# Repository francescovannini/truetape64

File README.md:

# TrueTape64

A cheap, easy to build adapter to interface a [Commodore 1530 (C2N) Datasette ](https://en.wikipedia.org/wiki/Commodore_Datasette) to your PC to dump and preserve your aging Commodore 64 software collection, as accurately as possible.

## What?!

Back in the '80s, many home computers used audio cassette tapes as a medium to to store data. Floppy disks already existed but they often required complex, dedicated hardware; tapes and tape decks on the other hand were cheap, common medium used for music and required simpler or in some cases (like Apple-II) no extra hardware or peripheral. Data was stored encoded as audio and it sounded very similar to the well-known squeaky modem / fax sounds. This storage method had obviously several downsides: long loading/saving times, wasn't "random access" so it required the user to manually advance the tape to the right position to access the desired file; and reliability depended a lot on the quality of the tape. But all these were more than acceptable compromises to keep the prices of these systems down and give everyone a cheap, good-enough way to access or build large software libraries.

As many other future developers born in the '80s, I've started writing BASIC code on a [Commodore 64](https://en.wikipedia.org/wiki/Commodore_64) when I was just a kid. Being still today a huge fan of this platform and having a large collection of tapes, during the past years I've found myself thinking about how to save all this data from the inevitable demise of its aging physical support. 

COVID-19 pandemic gave me some time to finally see if I could figure out how to do that and have some fun while doing it.

### But it has already been done...

Yes, this is certainly not the first project that addresses this issue; in fact I've tried a bunch of existing solutions in the past ([here](http://www.zimmers.net/anonftp/pub/cbm/crossplatform/transfer/datassette/index.html) a comprehensive list) before deciding to design my own device. 

One common approach is based only on clever software: the content of the tape is digitized via a standard audio tape deck (meant for music) connected to the input of a PC sound card. The software then analyzes the audio and extracts the data, performing a variety of corrections and fixes if necessary. This method is quite often the first that many people try, including myself, and usually it is good enough. It requires no weird hardware, however at least in my experience, it requires instead some trial and error; fiddling with volume levels, trying different tape decks and dumping the same tape multiple times to be sure it has been read correctly is the norm. This is because the hardware (tape deck and sound card) is designed for music, not for squeaky, highly-pitched noises. These kind of sounds can be very sensible to things like tape [wow and flutter](https://en.wikipedia.org/wiki/Wow_and_flutter_measurement) and to audio equalization or noise reduction filters; things designed to improve music, not data stored as audio.

Another less common approach involves hooking up the original Datassette to the PC via some sort of adapter. The roughest of these is probably [this one](http://web.archive.org/web/20071130192830/http://www.phs-edv.de/c64s/doc/lpt64.htm) which uses nothing more than a cable and the old-fashioned PC parallel port. This kind of approach requires some skills in building a bit of hardware and it also needs the original Datassette. However, the significant advantage over the software-only approach is that the output dump is closer to what a real Commodore machine would produce or ingest. This is due to the fact that the Datassette is a piece of dedicated hardware, featuring on-board specialized circuitry to clean and digitize the signal so that can be fed directly into the Commodore computer. 

### Design goals

I wanted this project to:

1) Be accurate: given a physical tape, loading it with a real C64 and its Datassette would produce the exact same result than loading the dump of that tape into an emulator when the dump is produced by the same Datassette coupled with this project
2) Be as simple as possible to build and use; bare minimum number of components, designed to be electrically tolerant, safe to use with vintage hardware and requiring minimal tuning; a companion software that does one thing only, but it does it well
3) Be pandemic-proof: all components needed to build the hardware are already in my junk drawer or are easy to obtain from online retailers
3) Be open source: there are similar commercially available devices, not all of them come with schematics or firmware source code. This one does.
4) Be fun and nostalgia fuelled: fiddle with technology designed at the end of the '70s, play with your favourite computer and, in the process, rescue code you wrote when you were 7.

What I've gotten so far:

* a simple hardware device that can be assembled in an hour for less than 10€
* a firmware for the Atmel AVR ATTiny2313 microcontroller which runs the device
* a simple Python command line tool that communicates with the microcontroller and generates a TAP dump of your tape

### Theory of operation

##### Pulse length encoding
The [TAP file format specifications](https://ist.uwaterloo.ca/~schepers/formats/TAP.TXT) gives already some good clues about how the data is stored on the tape and what the emulators such as [VICE](https://vice-emu.sourceforge.io/) expect to find. The Datassette page from [Wikipedia](https://en.wikipedia.org/wiki/Commodore_Datasette#Encoding) is also quite clear:

> To record physical data, the zero-crossing from positive to negative voltage of the analog signal is measured. The resulting time between these positive to negative crossings is then compared to a threshold to determine whether the time since the last crossing is short (0) or long (1).

In practice, the analog signal on the tape is a sine wave which goes from 0 to a minimum negative voltage, then to zero again, then to a maximum positive voltage and finally to zero again; this is fundamentally the entire sine period and it represents a "pulse". The hardware inside the Datassette converts the positive part into a TTL level equivalent to 1 and the negative part to a level equivalent to 0 and sends it over the cable.

This signal is then fed from the Datassette port directly into the C64 [Complex Interface Adapter (CIA)](https://www.c64-wiki.com/wiki/CIA) chip, which would simply run a counter clocked by the system clock to count how many clock cycles the sine period took to complete. In practice, the CIA measures how much time passed between two consecutive falling edges: 
* beginning of the current sine period: negative half-wave on tape, falling edge as seen by the CIA
* end of the current sine period, positive half-wave approaching 0, falling edge as seen by the CIA

If instead of feeding this signal to the CIA we feed it to a microcontroller with a fast enough clock, we could accurately capture the pulse length and then send it somehow to the software running on PC side; tihs is the basic principle behind this project. 

#### Clock speed

But how fast this clock needs to be? The original Commodore LOAD/SAVE routines in the C64 Kernal were designed to be resilient; they used long period pulses producing a relatively low frequency sound which could be safely stored even by low grade tape, but on the other hand loading/saving time were quite long. 

Developers quickly figured out that they could use their own routine to interact directly with the CIA and measure the lenght of each pulse, allowing them to use arbitrary pulse lengths, including very short ones; shorter pulses naturally meant faster loading time. [This article from COMPUTE! magazine](https://www.atarimagazines.com/compute/issue57/turbotape.html) from February 1985 gives an awesome (for a magazine) technical explanation about a popular "tape loader" of the era. Tape loaders were many so many are the different encodings you can find on old tapes. It's therefore obvious that we can't make any assumption on the length of the pulses we could find on the tape; we have to build something that can sample the shortest pulse the CIA can sample. 

We could run the microcontroller at the same clock speed used by the CIA, right? Yes, but how about running it more than TWICE as fast instead? This would ensure we capture data with twice the accuracy as the CIA would do.

##### Sending data over the PC

Once the pulse length is detected we need to send it to our software counterpart running on the PC for it to assemble into the output TAP file. Our microcontroller has a serial port that is fast enough to cope with the bitstream coming from the tape so interfacing that with a ultra common USB adapter is quite convenient. This also provides power to the entire system via the USB port.

##### The Datassette tape motor

The Datassette requires two input voltages: a 5V for the TTL logic and a ~6V for the tape motor.  As visible from the original C64 schematics, the C3 pin is fed from the unregulated 9V supplied by the power brick via a transistor and a 6.8V zener diode. This results in a quite stable ~6V output. However the motor voltage isn't critical; each datassette has a slightly different tape speed due to its rudimental mechanics, plus there are different models of Datassette around so the C64 has to be tolerant when measuring pulse length. 

To keep things simple, we opted to include a common DC-DC boost converter to take care of raising the voltage from the USB port from 5V to around 6.1V. Some similar projects use 5V for the motor, running the tape a bit slower and relying on software to compensate for this. I did not try this approach as I was aiming at accuracy but perhaps it would work good enough.

### Schematics and parts

Parts:

* [Atmel ATTiny2313-20PU](http://ww1.microchip.com/downloads/en/DeviceDoc/Atmel-2543-AVR-ATtiny2313_Datasheet.pdf)
* 16MHz crystal
* 33pF ceramic capacitors (2x)
* 10KΩ resistor
* 1KΩ resistor
* Red LED
* DC-DC booster module (for example, [this one](https://www.amazon.com/Converter-Voltage-Adjustable-Step-up-Circuit/dp/B07XG323G8/))
* FTDI232 serial to USB adapter (for example, [this one](https://www.amazon.com/HiLetgo-FT232RL-Converter-Adapter-Breakout/dp/B00IJXZQ7C/))
* Datassette edge connector (for example, [this one](https://www.ebay.com/itm/233499875028))
* 5x7 Perf board (for example [this one](https://www.amazon.com/uxcell-Universal-Printed-Circuit-Soldering/dp/B07FK5DWHR))
* 6 pins female header connector

The Datassette READ line is fed directly into PD6/ICP of the uC. This pin is the Input Capture Pin of the 16-bit Timer/Counter1 which can be programmed to generate an interrupt every time a falling edge is detected. The timer runs freely until either an overflow or a falling edge interrupt occurs. In the second case, this allows us to "timestamp" the edge with the value from the counter. 

The clock for the Timer/Counter1 is obtained by dividing by 8 the main clock, which is provided by the 16MHz crystal, giving a 2MHz sample rate. The C64 PAL clock (which is the default in the TAP format) is 985248Hz, so we are more than twice as fast. This should be more than enough to sample tapes for the NTSC model too (which runs at 1.023MHz) although this would probably require a little fix in the Python code. I have no NTSC tapes so I can't test this.

The SENSE line from the Datassette is essentially the output of a microswitch which is closed when one of the buttons on the Datassette is pressed. This is what makes the C64 detect that you "PRESSed PLAY ON TAPE". We capture this event with the micro and forward it to the Python client via the CTS line of the serial port hooked to PD3.

The led is there to signal "buffer overflow" conditions, which should normally never happen. A buffer overflow happens if the data rate from the tape exceeds the data rate of the serial port. We run the serial port at 250Kbps which should be more than enough for most tapes; however, since there is no hardware or software signaling implemented to notify the Python client that an overflow happened, you need to check this led at the end of the dump. If it had turned on, reset the device and try again.

Everything is powered by the USB port, including the DC-DC boost converter for the motor. 

### First (and probably last) prototype

Given the simplicity, the whole thing can be built on a perf board or even a breadboard if you don't need a permanent solution. Here the first prototype. The XL6009 booster board is hot-glued on top of the perfboard and connected with rigid wires.

**Adjust the DC-DC boost converter before hooking up a Datassette!** 

Hook up a multimeter between the MOTOR and the GND pins of the Datassette edge connector; using a flat screwdriver, turn the screw on the converter until you read about 6.15V on the multimeter. Now connect the Datassette, put a tape into it and press PLAY. If the voltage drops below 6.1V, adjust the screw again. In any circumstance, be sure the booster never outputs more than 6.5V or you would risk damaging your Datassette motor.

### AVR Firmware

The directory [avr](./avr) in this repo contains the source code of the ATTiny2313 firmware that runs the show on the adapter side. The file `truetape64.hex` is a pre-compiled version of the firmware that you can flash directly onto the AVR using the included Bash script. This script requires avrdude and the usbtiny programmer: check [Lady Ada tutorial](https://learn.adafruit.com/usbtinyisp/avrdude) for further instructions. 

If you flash with your own tool / programmer, remember to also program the fuses:

```
low: 0xFF
high: 0xDF
```

### Python CLI

A simple Python tool is included in the [cli](./cli) directory. The tool opens the serial port of the FTDI adapter and monitors its CTS line; when PLAY is pressed on the Datassette, the tool starts reading the data sent from the microcontroller. After some basic math to account for the differences in frequency between the AVR and the C64 PAL clock, the pulse length is written to the TAP file. The process continues until the CTS line status changes; this can happen either when the tape stops or when there is a buffer overflow; in the latter case, led on the board will be flashing fast until the tape is stopped.

The TAP v2 file format allows for pulse length values for up to 0xFFFFFF (3 bytes). The microcontroller always sends 3 bytes for each pulse, followed by a checksum byte. The checksum is just an extra measure to ensure there is no data corruption during the transfer between the microcontroller and the FTDI adapter, for instance due to a bad solder joint.

See the [README](./cli/) included with the tool for further instructions.

## Write support

This project is read-only by design: it can dump tapes, but it cannot write data back to a tape. Write support is technically possible on this hardware platform, but I have no plan to implement it in the near future. That said, I would be happy to review pull requests from anyone interested in adding it.

In the meantime, if you need write support today, have a look at the [projects inspired by TrueTape64](#projects-inspired-by-truetape64) below — some of them already implement it.

## Projects inspired by TrueTape64

It's been incredibly rewarding to see that this little project has, directly or indirectly, sparked other people's curiosity and inspired them to build their own takes on the same idea. Here are the ones I'm aware of:

* [C64_TapeDump64](https://github.com/wagiminator/C64-Collection/tree/master/C64_TapeDump64) by wagiminator
* [C64_TapeBuddy64](https://github.com/wagiminator/C64-Collection/tree/master/C64_TapeBuddy64) by wagiminator (evolution of C64_TapeDump64, adds write support)
* [TapeMate64](https://github.com/heneault/TapeMate64) by heneault (based on C64_TapeBuddy64)
* [Tapeosaurus](https://github.com/fabriziofiorucci/Tapeosaurus) by fabriziofiorucci

If TrueTape64 inspired your own project and it's not on this list, please open a PR to add it!

## As seen on Hackaday

This project has been featured on [Hackaday](https://hackaday.com/2021/05/10/truetape64-is-a-pc-interface-for-your-c64-datasette/)

## License
[GPLv3](./LICENSE)

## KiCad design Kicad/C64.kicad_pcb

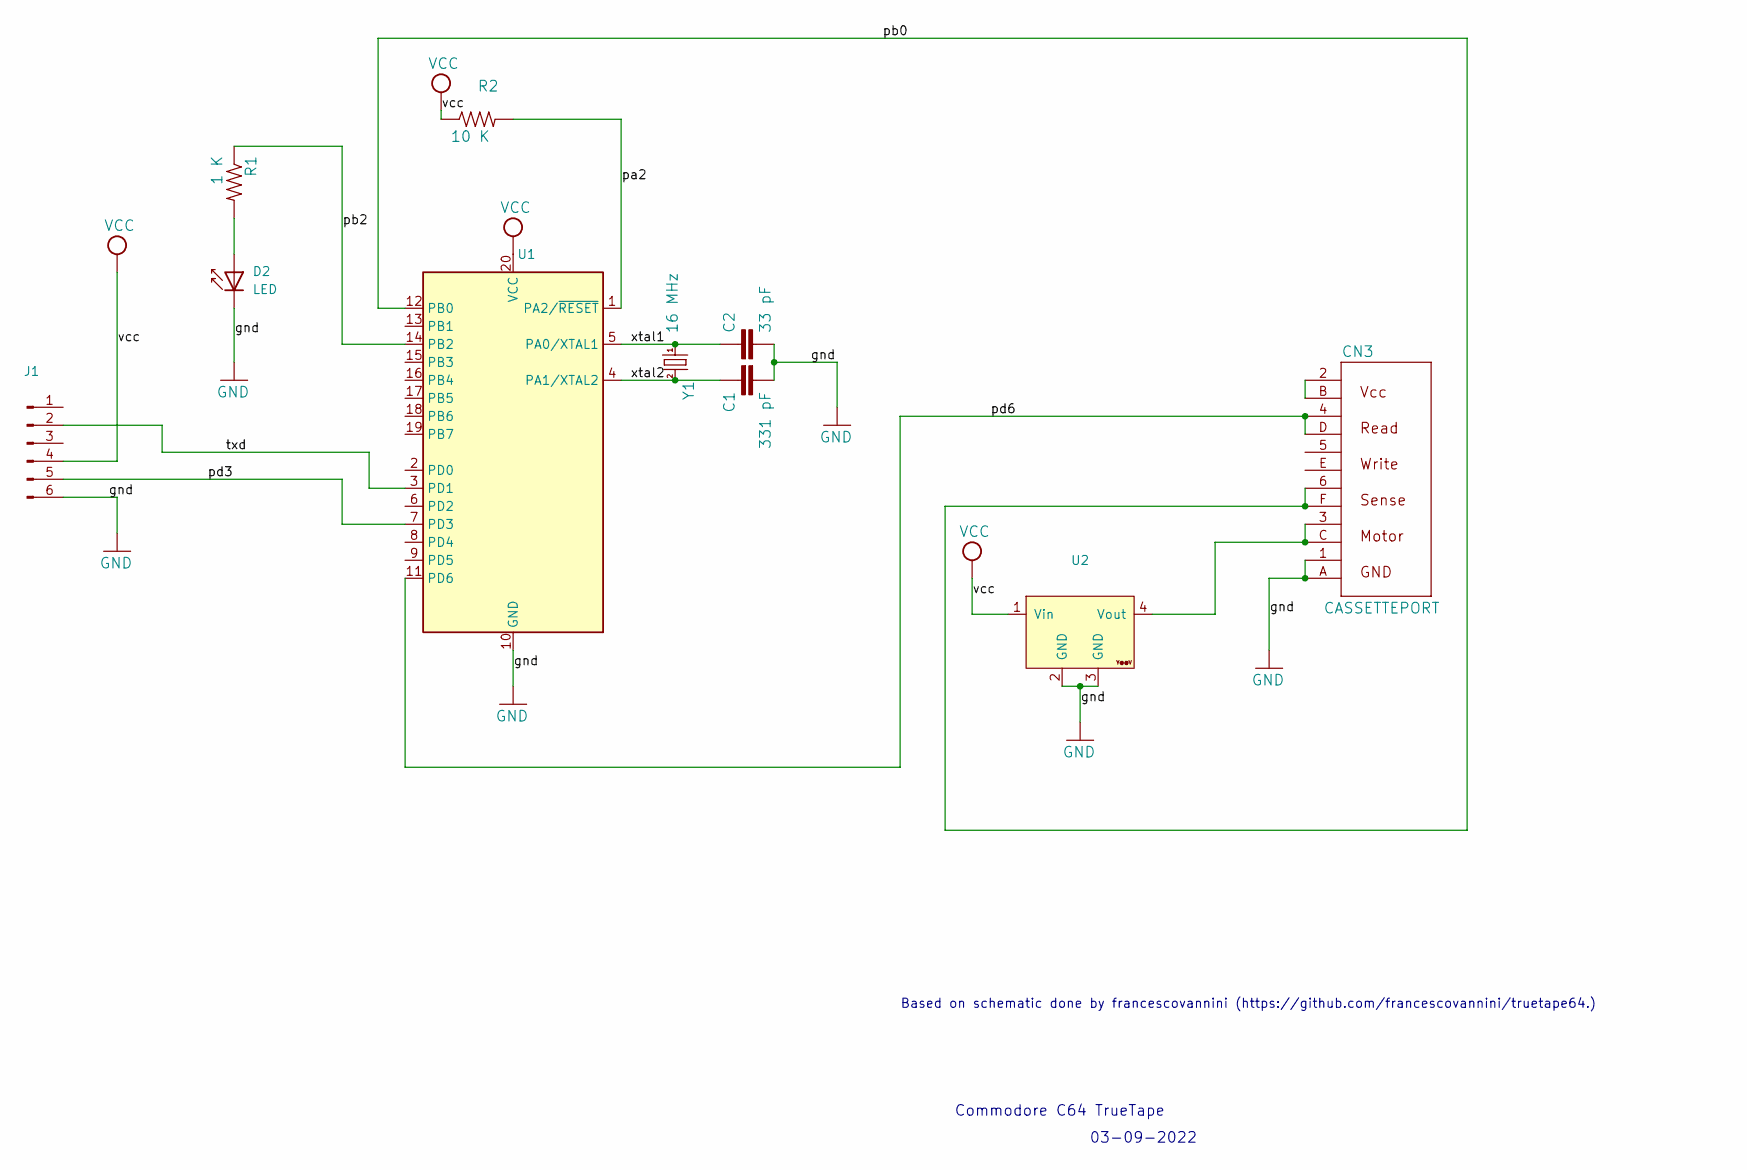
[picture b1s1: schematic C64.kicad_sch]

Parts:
C1: 331 pF; 0203
C2: 33 pF; 0203
CN3: CASSETTEPORT
D2: LED; LED_D5.0mm_IRGrey
J1: Conn_01x06_Male; PinHeader_1x06_P2.54mm_Vertical
R1: 1 K; R_Axial_DIN0414_L11.9mm_D4.5mm_P7.62mm_Vertical
R2: 10 K; R_Axial_DIN0414_L11.9mm_D4.5mm_P7.62mm_Vertical
U1: ATtiny2313-20P; DIP-20_W7.62mm
U2: YAAJ_DCDC_StepDown_LM2596
Y1: 16 MHz; HC49TL-H

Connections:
/pa2: R2.2, U1.1 (PA2/~RESET)
/pb0: CN3.6 (SENSE1), CN3.F (SENSE2), U1.12 (PB0)
/pb2: R1.1, U1.14 (PB2)
/pd3: J1.5, U1.7 (PD3)
/pd6: CN3.4 (READ1), CN3.D (READ2), U1.11 (PD6)
/txd: J1.2, U1.3 (PD1)
/xtal1: C2.1, U1.5 (PA0/XTAL1), Y1.1
/xtal2: C1.1, U1.4 (PA1/XTAL2), Y1.2
GND: C1.2, C2.2, CN3.1 (GND1), CN3.A (GND2), D2.1 (K), J1.6, U1.10 (GND), U2.2 (GND), U2.3 (GND)
unnamed: CN3.2 (VCC1), CN3.B (VCC2)
unnamed: CN3.3 (MOTOR1), CN3.C (MOTOR2), U2.4 (Vout)
unnamed: D2.2 (A), R1.2
VCC: J1.4, R2.1, U1.20 (VCC), U2.1 (Vin)

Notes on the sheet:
Based on schematic done by francescovannini (https://github.com/francescovannini/truetape64.)
03-09-2022
Commodore C64 TrueTape

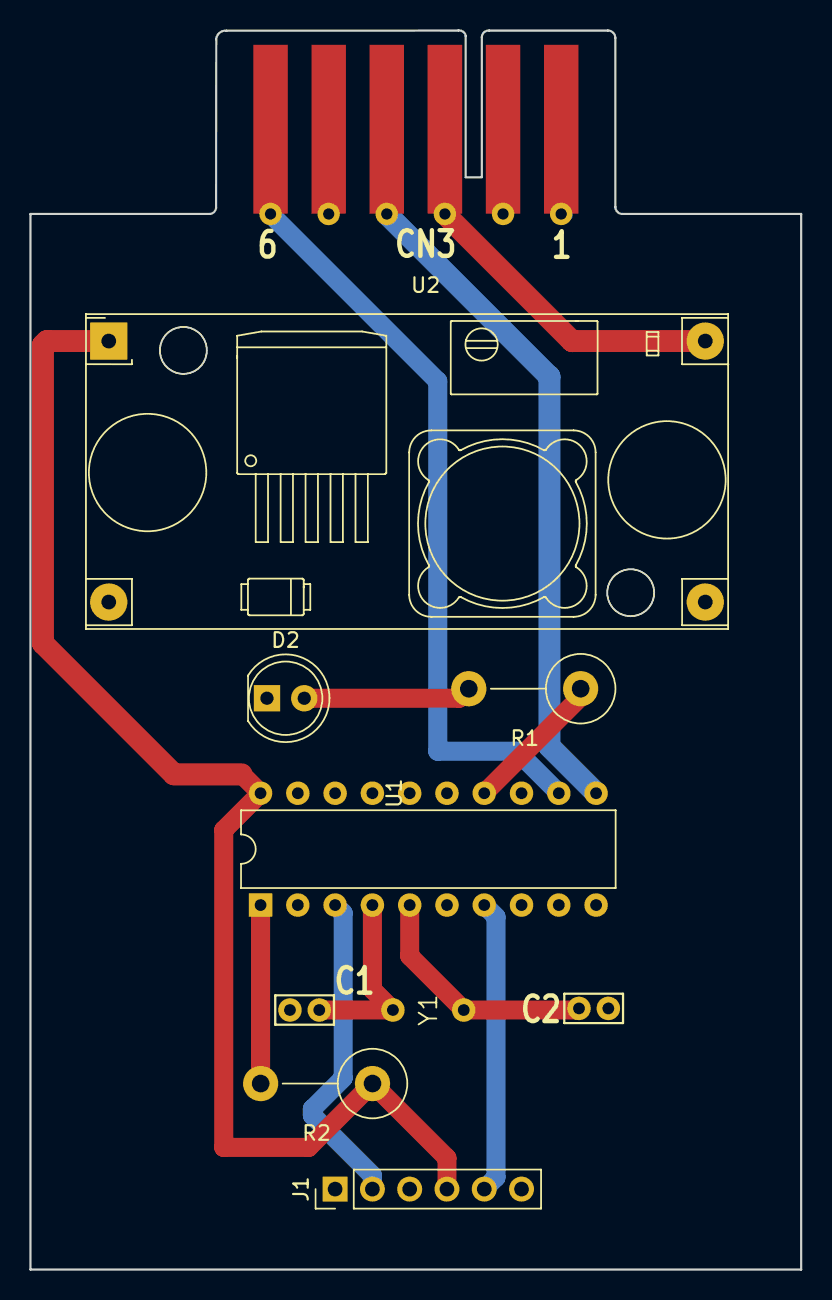
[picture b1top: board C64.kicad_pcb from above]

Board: 2 copper layers, 52.5 x 84.4 mm, 10 parts (0 on the bottom side), 13 nets.

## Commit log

2020-12-29 Initial commit, working Works with XTAL = 16MHz, uses C64 PAL clock Added argument parsing Error handling Code cleanup Moved to cli subdir
2021-05-02 Move led to PB2 while building prototype board Code cleanup
2021-05-02 Working firmware
2021-05-02 Added setup Added README.md
2021-05-02 Fixed sense PIN Added documentation Repo cleanup
2021-05-02 Fixed LICENSE files
2022-01-09 Fixed sense pin in documentation
2022-02-06 Incomplete, dumping works ok. Rewrote buffers Interrupt driven
2022-02-12 Incomplete New message format New checksum routine Accurate long pulses
2022-02-13 Incomplete Fixed checksum calculation (using bit shift) Added msg.c/h and cleanup
2022-05-26 Update 'README.md'
2022-05-26 Build tools cleanup
2022-05-29 Initial successful waveform generation based on data from Python
2022-05-29 Compiler flags for size optimization
2022-06-04 More compiler flags
2022-06-04 Make the compiler happy
2022-06-04 Working stream writing New SM states UART double speed Last commit before removing the checksum
2022-06-04 Removed checksum, using only serial parity
2022-08-15 Rewrote msgqueue to better use memory Works better, can reach lower than 700us pulse length Still lots to do
2022-08-28 More improvements, rewrote a lot of stuff. Can reach about sustained 300us pulse length Added setserial to reduce serial latency (super critical!)
2022-08-28 Fixes
2022-08-28 Lots of changes
2022-10-08 Cleanup and better logging
2023-07-03 Fixed pre-compiled firmare
2023-07-04 Cleanup
2023-09-25 Added Simple Kicad Design
2026-06-22 Add write support and inspired projects sections to README

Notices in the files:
README.md:
[GPLv3](./LICENSE)
